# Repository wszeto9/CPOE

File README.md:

# CPOE
 Cheap PoE. Not according to protocol, just trying to use cheap ethernet cables as power wiring.

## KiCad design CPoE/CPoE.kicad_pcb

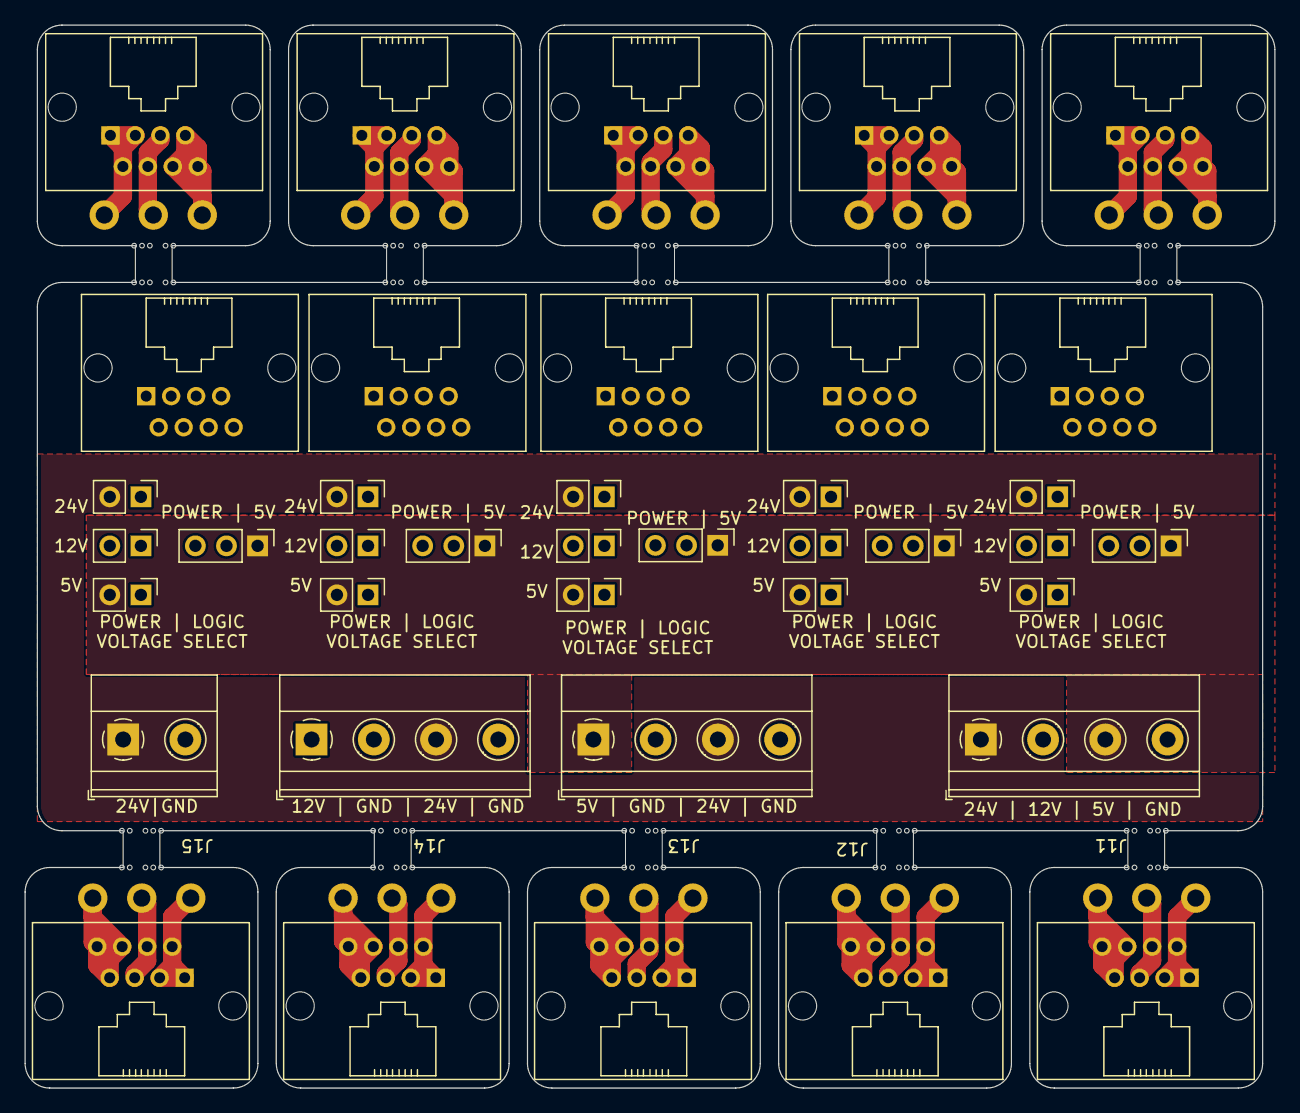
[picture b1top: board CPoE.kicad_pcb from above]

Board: 2 copper layers, 102.0 x 86.8 mm, 49 parts (0 on the bottom side), 24 nets.

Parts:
J1, J1#2: RJ45_SINK1; RJ45_5501-88011111
J2, J2#2: RJ45_SINK2; RJ45_5501-88011111
J3, J3#2: RJ45_SINK3; RJ45_5501-88011111
J4, J4#2: RJ45_SINK4; RJ45_5501-88011111
J5, J5#2: RJ45_SINK5; RJ45_5501-88011111
J6, J6#2: SINK1; 1x03_16AWG_Wire2Board
J7, J7#2: SINK2; 1x03_16AWG_Wire2Board
J8, J8#2: SINK3; 1x03_16AWG_Wire2Board
J9, J9#2: SINK4; 1x03_16AWG_Wire2Board
J10, J10#2: SINK5; 1x03_16AWG_Wire2Board
J11: RJ45_SOURCE1; RJ45_5501-88011111
J12: RJ45_SOURCE2; RJ45_5501-88011111
J13: RJ45_SOURCE3; RJ45_5501-88011111
J14: RJ45_SOURCE4; RJ45_5501-88011111
J15: RJ45_SOURCE5; RJ45_5501-88011111
J16: 24VIN; TerminalBlock_Phoenix_MKDS-1,5-2-5.08_1x02_P5.08mm_Horizont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
J17: 12V_BUCK; TerminalBlock_Phoenix_MKDS-1,5-4-5.08_1x04_P5.08mm_Horizont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
J18: 5V_BUCK; TerminalBlock_Phoenix_MKDS-1,5-4-5.08_1x04_P5.08mm_Horizont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
J19: POWER_RAILS; TerminalBlock_Phoenix_MKDS-1,5-4-5.08_1x04_P5.08mm_Horizont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
JP1: LOGIC_V_1; PinHeader_1x03_P2.54mm_Vertical
JP2: LOGIC_V_2; PinHeader_1x03_P2.54mm_Vertical
JP3, JP4, JP5: LOGIC_VOLTAGE; PinHeader_1x03_P2.54mm_Vertical
JP6, JP8, JP9, JP10: P5V_1; PinHeader_1x02_P2.54mm_Vertical
JP7: P5V_2; PinHeader_1x02_P2.54mm_Vertical
JP11, JP13, JP14, JP15: P12V_1; PinHeader_1x02_P2.54mm_Vertical
JP12: P12V_2; PinHeader_1x02_P2.54mm_Vertical
JP16, JP18, JP19, JP20: P24V_1; PinHeader_1x02_P2.54mm_Vertical
JP17: P24V_2; PinHeader_1x02_P2.54mm_Vertical

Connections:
+5V: J18.1, J19.3, JP1.1 (A), JP2.1 (A), JP3.1 (A), JP4.1 (A), JP5.1 (A), JP6.2 (B), JP7.2 (B), JP8.2 (B), JP9.2 (B), JP10.2 (B)
+12V: J17.1, J19.2, JP11.2 (B), JP12.2 (B), JP13.2 (B), JP14.2 (B), JP15.2 (B)
+24V: J16.1, J17.3, J18.3, J19.1, JP16.2 (B), JP17.2 (B), JP18.2 (B), JP19.2 (B), JP20.2 (B)
/LOGIC_V1: J11.4, J11.5, JP1.2 (C)
/LOGIC_V2: J12.4, J12.5, JP2.2 (C)
/LOGIC_V3: J13.4, J13.5, JP3.2 (C)
/LOGIC_V4: J14.4, J14.5, JP4.2 (C)
/LOGIC_V5: J15.4, J15.5, JP5.2 (C)
/POWER_V1: J11.1, J11.2, J11.3, JP1.3 (B), JP6.1 (A), JP11.1 (A), JP16.1 (A)
/POWER_V2: J12.1, J12.2, J12.3, JP2.3 (B), JP7.1 (A), JP12.1 (A), JP17.1 (A)
/POWER_V3: J13.1, J13.2, J13.3, JP3.3 (B), JP8.1 (A), JP13.1 (A), JP18.1 (A)
/POWER_V4: J14.1, J14.2, J14.3, JP4.3 (B), JP9.1 (A), JP14.1 (A), JP19.1 (A)
/POWER_V5: J15.1, J15.2, J15.3, JP5.3 (B), JP10.1 (A), JP15.1 (A), JP20.1 (A)
GND: J1.6, J1.7, J1.8, J1#2.6, J1#2.7, J1#2.8, J2.6, J2.7, J2.8, J2#2.6, J2#2.7, J2#2.8, J3.6, J3.7, J3.8, J3#2.6, J3#2.7, J3#2.8, J4.6, J4.7, J4.8, J4#2.6, J4#2.7, J4#2.8, J5.6, J5.7, J5.8, J5#2.6, J5#2.7, J5#2.8, J6.1, J6#2.1, J7.1, J7#2.1, J8.1, J8#2.1, J9.1, J9#2.1, J10.1, J10#2.1, J11.6, J11.7, J11.8, J12.6, J12.7, J12.8, J13.6, J13.7, J13.8, J14.6, J14.7, J14.8, J15.6, J15.7, J15.8, J16.2, J17.2, J17.4, J18.2, J18.4, J19.4
unnamed: J1.1, J1.2, J1.3, J1#2.1, J1#2.2, J1#2.3, J6.3, J6#2.3
unnamed: J1.4, J1.5, J1#2.4, J1#2.5, J6.2, J6#2.2
unnamed: J2.1, J2.2, J2.3, J2#2.1, J2#2.2, J2#2.3, J7.3, J7#2.3
unnamed: J2.4, J2.5, J2#2.4, J2#2.5, J7.2, J7#2.2
unnamed: J3.1, J3.2, J3.3, J3#2.1, J3#2.2, J3#2.3, J8.3, J8#2.3
unnamed: J3.4, J3.5, J3#2.4, J3#2.5, J8.2, J8#2.2
unnamed: J4.1, J4.2, J4.3, J4#2.1, J4#2.2, J4#2.3, J9.3, J9#2.3
unnamed: J4.4, J4.5, J4#2.4, J4#2.5, J9.2, J9#2.2
unnamed: J5.1, J5.2, J5.3, J5#2.1, J5#2.2, J5#2.3, J10.3, J10#2.3
unnamed: J5.4, J5.5, J5#2.4, J5#2.5, J10.2, J10#2.2

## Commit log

2022-08-22 laid out components
